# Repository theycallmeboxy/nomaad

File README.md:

# Nomaad
*A 11 column ortho/alpha gaming keyboard for gamers*

**[KLE](https://www.keyboard-layout-editor.com/##@_name=Nomaad%20Vial&author=theycallmeboxy%3B&@_x:0.5%3B&=0,1&=0,2&=0,3&=0,4&=0,5%3B&@=1,0&=1,1&=1,2&=1,3&=1,4&=1,5&=1,6&=1,7&=1,8&=1,9&=1,10%3B&@=2,0&=2,1&=2,2&=2,3&=2,4&=2,5&=2,6&=2,7&=2,8&=2,9&=2,10%3B&@_c=%2300c5ff%3B&=3,0%0A%0A%0A0,0&=3,1%0A%0A%0A0,0&=3,2%0A%0A%0A0,0&=3,3%0A%0A%0A0,0&=3,4%0A%0A%0A0,0&=3,5%0A%0A%0A0,0&=3,6%0A%0A%0A0,0&=3,7%0A%0A%0A0,0&=3,8%0A%0A%0A0,0&=3,9%0A%0A%0A0,0&=3,10%0A%0A%0A0,0%3B&@_c=%23cccccc%3B&=4,0&_x:1&c=%23ffb80c%3B&=4,1%0A%0A%0A1,0&_w:3%3B&=4,3%0A%0A%0A1,0&_w:2%3B&=4,6%0A%0A%0A1,0&=4,7%0A%0A%0A1,0&_x:1&c=%23cccccc%3B&=4,10%3B&@_y:0.5&c=%2300c5ff&w:1.5%3B&=3,0%0A%0A%0A0,1&=3,1%0A%0A%0A0,1&=3,2%0A%0A%0A0,1&=3,3%0A%0A%0A0,1&=3,4%0A%0A%0A0,1&=3,5%0A%0A%0A0,1&=3,6%0A%0A%0A0,1&=3,7%0A%0A%0A0,1&=3,8%0A%0A%0A0,1&_w:1.5%3B&=3,10%0A%0A%0A0,1%3B&@_y:0.25&x:2&c=%23ffb80c&w:7%3B&=4,3%0A%0A%0A1,1)**

## Production Files:

*(Click a link then click download icon in the top right to save a given file to your computer.)*

> [!CAUTION]
> I will assume no responsibility for any cost, damage, or sads resulting from trying to make one of my dumb projects. This project has no implicit support, neither moral nor technical.
> 
> **I'm not a doctor. This is not medical advice. I'm also only a network engineer. You assume all liability in using or reproducing these files.**

Case:
- [Case .stl file](https://github.com/theycallmeboxy/nomaad/blob/main/models/case/nomaad-case.stl)
- [Case .step file](https://github.com/theycallmeboxy/nomaad/blob/main/models/case/nomaad-case.step)

Plate:
- [Ortho stagger plate .dxf file](https://github.com/theycallmeboxy/nomaad/blob/main/models/plate/nomaad-plate_ortho.dxf)
- [Alpha stagger plate .dxf file](https://github.com/theycallmeboxy/nomaad/blob/main/models/plate/nomaad-plate_alpha.dxf)

PCB:
> [!NOTE]
> Version 1 was produced (as prototype 1) without any identified issues.  The gerbers were regenerated to indicate version 1 on the silk and the bom and positions files should be fixed to order as-is.  I have not produced these files yet, but they should be good to go.

- [PCB gerbers .zip file](https://github.com/theycallmeboxy/nomaad/blob/main/pcb/nomaad%20v1/production/nomaad.zip)
- [BOM .csv file](https://github.com/theycallmeboxy/nomaad/blob/main/pcb/nomaad%20v1/production/bom.csv)
- [Positions .csv file](https://github.com/theycallmeboxy/nomaad/blob/main/pcb/nomaad%20v1/production/positions.csv)

Firmware:
- [VIAL Firmware .bin file](https://github.com/theycallmeboxy/nomaad/blob/main/firmware/vial/binary/boxy_nomaad_vial.bin)
  
## Build Notes:

I have made with FDM and CNC aluminum to good effect.  Another 40s member had a resin version manufactured successfully.

**Additional materials:**
 
  - About 18" of .139" (3.53mm) cross section o-ring cord [like this 50A cord](https://www.theoringstore.com/store/index.php?main_page=product_info&cPath=117_527&products_id=18618) or [this 70A cord](https://www.theoringstore.com/store/index.php?main_page=product_info&cPath=117_119&products_id=5058); if you don't want to buy bulk cord, you can cut up an o-ring of like 6" or bigger diameter.
  - 4 SKUF feet like these  [like these](https://keeb.io/products/skuf-silicone-rubber-keyboard-feet).

**Build instructions:**

1. Apply feet to the cutouts.
2. Install stabs if you're into that. 
3. Install switches into the plate and PCB.
4. Solder it up.
5. Friction fit the o-ring cord between the plate and PCB in the positions highlighted in red:

6. Insert the assembled PCB number keys first into the case at an angle while aligning the USB port with the cutout.
7. Press the top of the PCB in place, then press in the bottom side (if your cord isn't fully seated, sticks out on the corners, or otherwise catches going in, grab some tweezers and help it stay in between the plate and PCB). 
8. If you need to remove the PCB, pull a few caps off and use a switch puller on the soldered switches.

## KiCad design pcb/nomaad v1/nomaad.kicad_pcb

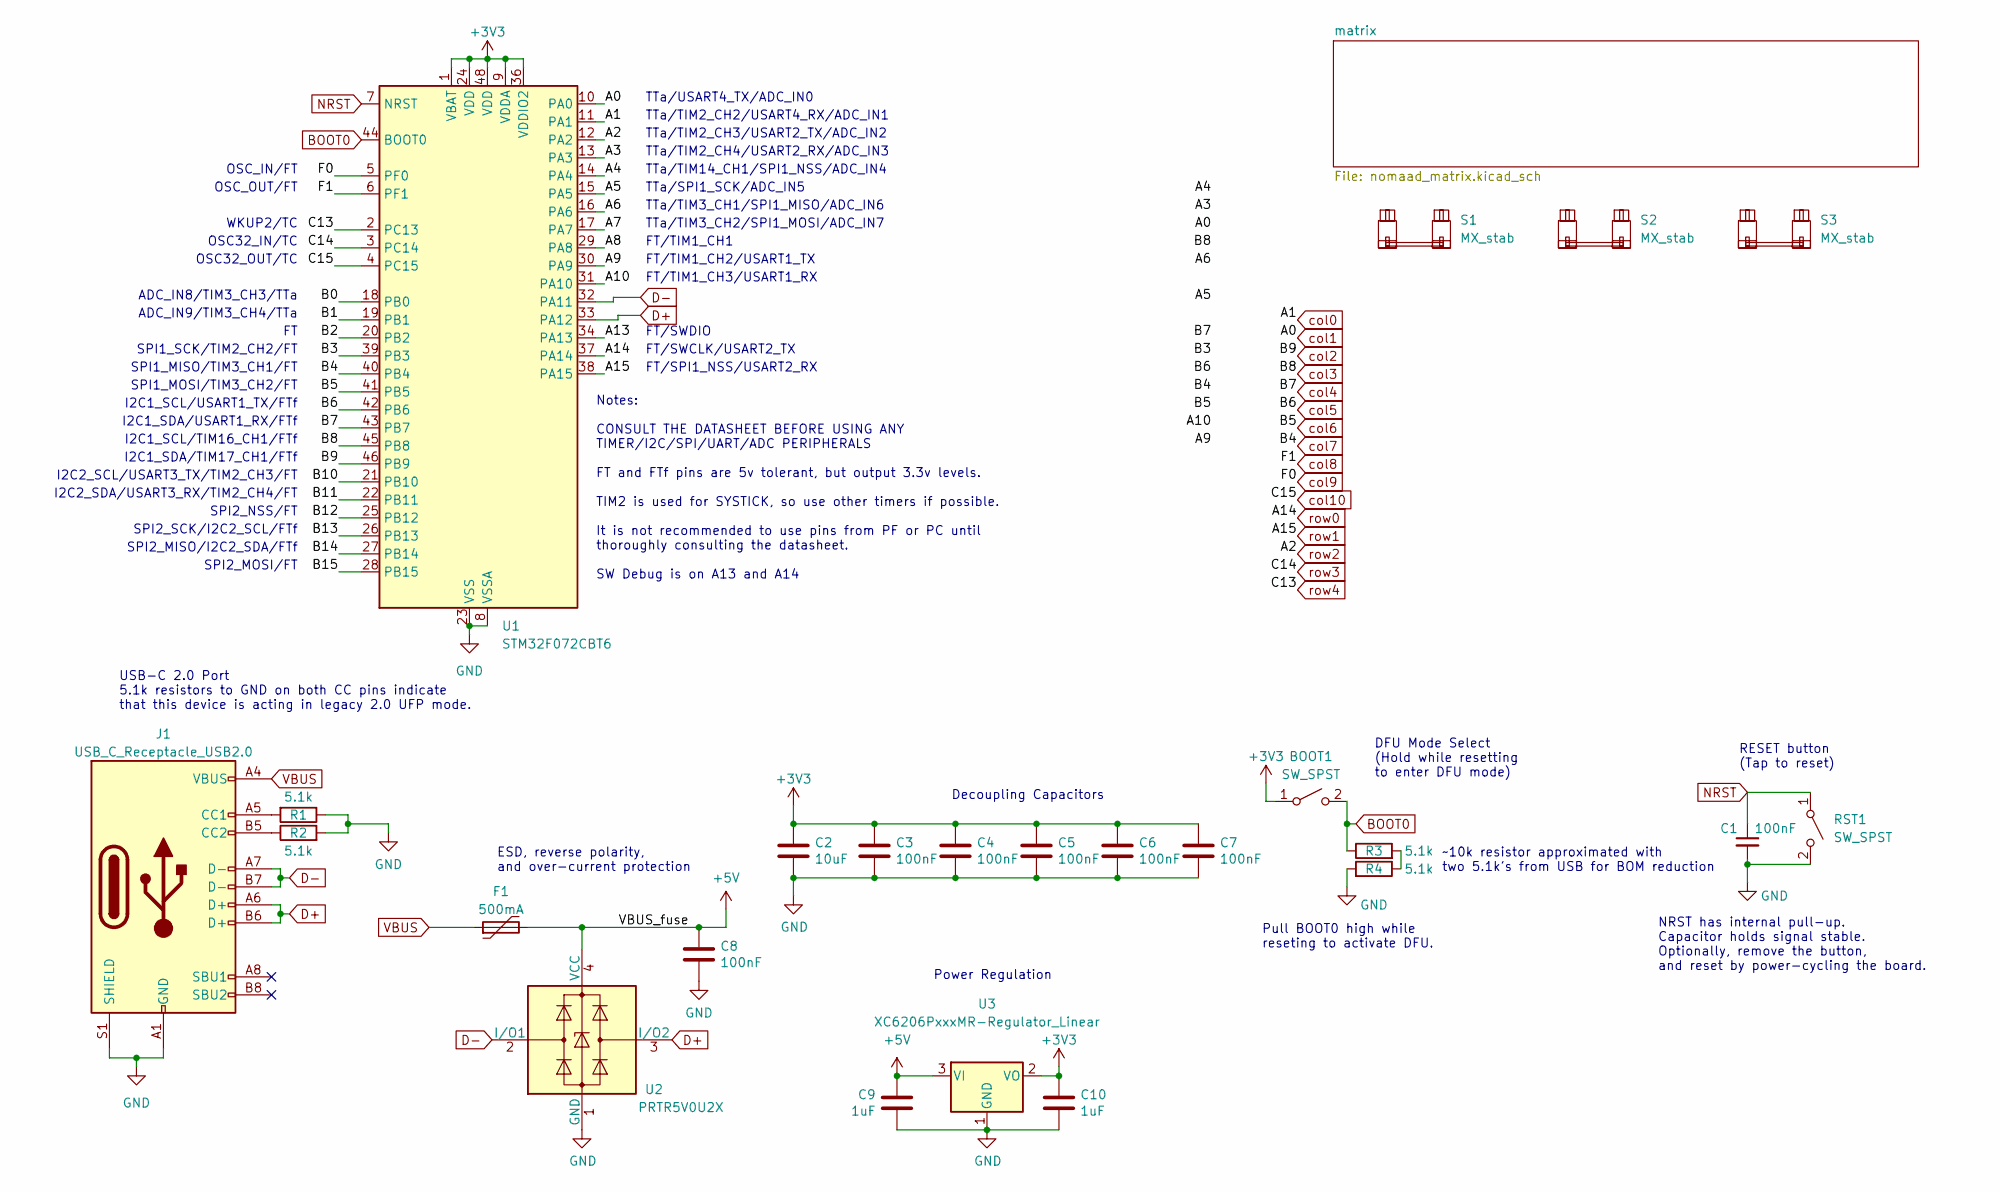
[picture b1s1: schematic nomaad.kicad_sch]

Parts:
BOOT1: SW_SPST; SW_SPST_TL3342
C1, C3, C4, C5, C6, C7, C8: 100nF; C_0402_1005Metric; LCSC C307331
C2: 10uF; C_0603_1608Metric; LCSC C307331
C9, C10: 1uF; C_0402_1005Metric; LCSC C307331
F1: 500mA; Fuse_1206_3216Metric; LCSC C135341
J1: USB_C_Receptacle_USB2.0; USB_C_Receptacle_HRO_TYPE-C-31-M-12; JlcRotOffset 180
R1, R2, R3, R4: 5.1k; R_0402_1005Metric
RST1: SW_SPST; SW_SPST_TL3342
S1: MX_stab; STAB_MX_7u
S2: MX_stab; STAB_MX_2u
S3: MX_stab; STAB_MX_3u
U1: STM32F072CBT6; LQFP-48_7x7mm_P0.5mm; JlcRotOffset 90
U2: PRTR5V0U2X; SOT-143; LCSC C2827688
U3: XC6206PxxxMR-Regulator_Linear; SOT-23; LCSC C5446

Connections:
+3V3: BOOT1.1 (A), C2.1, C3.1, C4.1, C5.1, C6.1, C7.1, C10.1, U1.1 (VBAT), U1.9 (VDDA), U1.24 (VDD), U1.36 (VDDIO2), U1.48 (VDD), U3.2 (VO)
+5V: C8.1, C9.1, F1.2, U2.4 (VCC), U3.3 (VI)
/A3: U1.13 (PA3)
/A4: U1.14 (PA4)
/A5: U1.15 (PA5)
/A6: U1.16 (PA6)
/A7: U1.17 (PA7)
/A8: U1.29 (PA8)
/A9: U1.30 (PA9)
/A10: U1.31 (PA10)
/A13: U1.34 (PA13)
/B0: U1.18 (PB0)
/B1: U1.19 (PB1)
/B2: U1.20 (PB2)
/B3: U1.39 (PB3)
/B10: U1.21 (PB10)
/B11: U1.22 (PB11)
/B12: U1.25 (PB12)
/B13: U1.26 (PB13)
/B14: U1.27 (PB14)
/B15: U1.28 (PB15)
BOOT0: BOOT1.2 (B), R3.1, U1.44 (BOOT0)
D+: J1.A6 (D+), J1.B6 (D+), U1.33 (PA12), U2.3 (I/O2)
D-: J1.A7 (D-), J1.B7 (D-), U1.32 (PA11), U2.2 (I/O1)
GND: C1.2, C2.2, C3.2, C4.2, C5.2, C6.2, C7.2, C8.2, C9.2, C10.2, J1.A1 (GND), J1.A12 (GND), J1.B1 (GND), J1.B12 (GND), J1.S1 (SHIELD), R1.1, R2.2, R4.2, RST1.2 (B), U1.8 (VSSA), U1.23 (VSS), U1.35 (VSS), U1.47 (VSS), U2.1 (GND), U3.1 (GND)
NRST: C1.1, RST1.1 (A), U1.7 (NRST)
unnamed: J1.A5 (CC1), R1.2
unnamed: J1.B5 (CC2), R2.1
unnamed: R3.2, R4.1
VBUS: F1.1, J1.A4 (VBUS), J1.A9 (VBUS), J1.B4 (VBUS), J1.B9 (VBUS)
col0: U1.11 (PA1); also elsewhere on the board
col1: U1.10 (PA0); also elsewhere on the board
col2: U1.46 (PB9); also elsewhere on the board
col3: U1.45 (PB8); also elsewhere on the board
col4: U1.43 (PB7); also elsewhere on the board
col5: U1.42 (PB6); also elsewhere on the board
col6: U1.41 (PB5); also elsewhere on the board
col7: U1.40 (PB4); also elsewhere on the board
col8: U1.6 (PF1); also elsewhere on the board
col9: U1.5 (PF0); also elsewhere on the board
col10: U1.4 (PC15); also elsewhere on the board
row0: U1.37 (PA14); also elsewhere on the board
row1: U1.38 (PA15); also elsewhere on the board
row2: U1.12 (PA2); also elsewhere on the board
row3: U1.3 (PC14); also elsewhere on the board
row4: U1.2 (PC13); also elsewhere on the board

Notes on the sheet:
I2C2_SCL/USART3_TX/TIM2_CH3/FT
TTa/TIM2_CH2/USART4_RX/ADC_IN1
OSC_IN/FT
Decoupling Capacitors
DFU Mode Select (Hold while resetting to enter DFU mode)
OSC32_IN/TC
SPI2_MISO/I2C2_SDA/FTf
SPI2_MOSI/FT
SPI1_SCK/TIM2_CH2/FT
I2C2_SDA/USART3_RX/TIM2_CH4/FT
OSC_OUT/FT
Power Regulation
TTa/TIM14_CH1/SPI1_NSS/ADC_IN4
Pull BOOT0 high while reseting to activate DFU.
FT/TIM1_CH2/USART1_TX
SPI2_SCK/I2C2_SCL/FTf
ADC_IN8/TIM3_CH3/TTa
TTa/SPI1_SCK/ADC_IN5
I2C1_SDA/TIM17_CH1/FTf
I2C1_SCL/USART1_TX/FTf
WKUP2/TC
FT/TIM1_CH1
TTa/USART4_TX/ADC_IN0
USB-C 2.0 Port 5.1k resistors to GND on both CC pins indicate that this device is acting in legacy 2.0 UFP mode.
ESD, reverse polarity, and over-current protection
NRST has internal pull-up. Capacitor holds signal stable. Optionally, remove the button, and reset by power-cycling the board.
OSC32_OUT/TC
~10k resistor approximated with two 5.1k's from USB for BOM reduction
I2C1_SDA/USART1_RX/FTf
TTa/TIM3_CH2/SPI1_MOSI/ADC_IN7
TTa/TIM2_CH4/USART2_RX/ADC_IN3
ADC_IN9/TIM3_CH4/TTa
SPI1_MOSI/TIM3_CH2/FT
FT/SPI1_NSS/USART2_RX
FT/SWCLK/USART2_TX
SPI2_NSS/FT
FT/SWDIO
I2C1_SCL/TIM16_CH1/FTf
FT/TIM1_CH3/USART1_RX
TTa/TIM3_CH1/SPI1_MISO/ADC_IN6

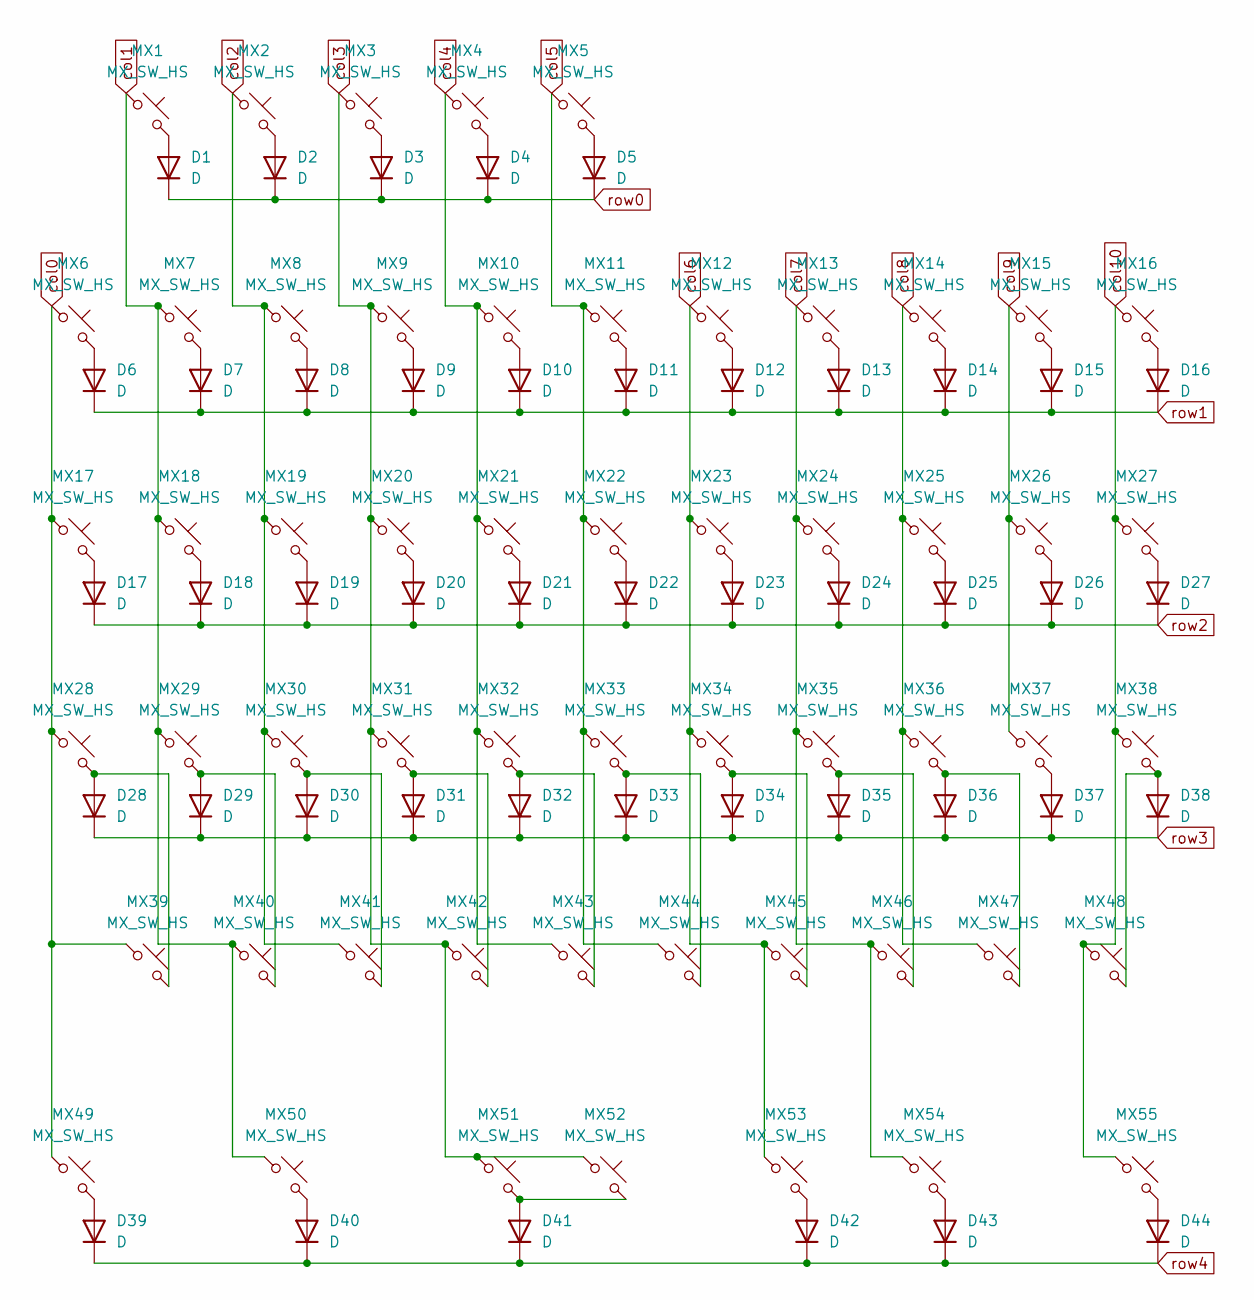
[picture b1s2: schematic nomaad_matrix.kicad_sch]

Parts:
D1, D2, D3, D4, D5, D6, D7, D8, D9, D10, D11, D12, D13, D14, D15, D16, D17, D18, D19, D20, D21, D22, D23, D24, D25, D26, D27, D28, D29, D30, D31, D32, D33, D34, D35, D36, D37, D38, D39, D40, D41, D42, D43, D44: D; D_SOD-123
MX1, MX2, MX3, MX4, MX5, MX6, MX7, MX8, MX9, MX10, MX11, MX12, MX13, MX14, MX15, MX16, MX17, MX18, MX19, MX20, MX21, MX22, MX23, MX24, MX25, MX26, MX27, MX28, MX29, MX30, MX31, MX32, MX33, MX34, MX35, MX36, MX37, MX38, MX39, MX40, MX41, MX42, MX43, MX44, MX45, MX46, MX47, MX48, MX49, MX50, MX51, MX52, MX53, MX54, MX55: MX_SW_HS; SW_MX_1u

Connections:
unnamed: D1.2 (A), MX1.2
unnamed: D2.2 (A), MX2.2
unnamed: D3.2 (A), MX3.2
unnamed: D4.2 (A), MX4.2
unnamed: D5.2 (A), MX5.2
unnamed: D6.2 (A), MX6.2
unnamed: D7.2 (A), MX7.2
unnamed: D8.2 (A), MX8.2
unnamed: D9.2 (A), MX9.2
unnamed: D10.2 (A), MX10.2
unnamed: D11.2 (A), MX11.2
unnamed: D12.2 (A), MX12.2
unnamed: D13.2 (A), MX13.2
unnamed: D14.2 (A), MX14.2
unnamed: D15.2 (A), MX15.2
unnamed: D16.2 (A), MX16.2
unnamed: D17.2 (A), MX17.2
unnamed: D18.2 (A), MX18.2
unnamed: D19.2 (A), MX19.2
unnamed: D20.2 (A), MX20.2
unnamed: D21.2 (A), MX21.2
unnamed: D22.2 (A), MX22.2
unnamed: D23.2 (A), MX23.2
unnamed: D24.2 (A), MX24.2
unnamed: D25.2 (A), MX25.2
unnamed: D26.2 (A), MX26.2
unnamed: D27.2 (A), MX27.2
unnamed: D28.2 (A), MX28.2, MX39.2
unnamed: D29.2 (A), MX29.2, MX40.2
unnamed: D30.2 (A), MX30.2, MX41.2
unnamed: D31.2 (A), MX31.2, MX42.2
unnamed: D32.2 (A), MX32.2, MX43.2
unnamed: D33.2 (A), MX33.2, MX44.2
unnamed: D34.2 (A), MX34.2, MX45.2
unnamed: D35.2 (A), MX35.2, MX46.2
unnamed: D36.2 (A), MX36.2, MX47.2
unnamed: D37.2 (A), MX37.2
unnamed: D38.2 (A), MX38.2, MX48.2
unnamed: D39.2 (A), MX49.2
unnamed: D40.2 (A), MX50.2
unnamed: D41.2 (A), MX51.2, MX52.2
unnamed: D42.2 (A), MX53.2
unnamed: D43.2 (A), MX54.2
unnamed: D44.2 (A), MX55.2
col0: MX6.1, MX17.1, MX28.1, MX39.1, MX49.1; also elsewhere on the board
col1: MX1.1, MX7.1, MX18.1, MX29.1, MX40.1, MX50.1; also elsewhere on the board
col2: MX2.1, MX8.1, MX19.1, MX30.1, MX41.1; also elsewhere on the board
col3: MX3.1, MX9.1, MX20.1, MX31.1, MX42.1, MX51.1, MX52.1; also elsewhere on the board
col4: MX4.1, MX10.1, MX21.1, MX32.1, MX43.1; also elsewhere on the board
col5: MX5.1, MX11.1, MX22.1, MX33.1, MX44.1; also elsewhere on the board
col6: MX12.1, MX23.1, MX34.1, MX45.1, MX53.1; also elsewhere on the board
col7: MX13.1, MX24.1, MX35.1, MX46.1, MX54.1; also elsewhere on the board
col8: MX14.1, MX25.1, MX36.1, MX47.1; also elsewhere on the board
col9: MX15.1, MX26.1, MX37.1; also elsewhere on the board
col10: MX16.1, MX27.1, MX38.1, MX48.1, MX55.1; also elsewhere on the board
row0: D1.1 (K), D2.1 (K), D3.1 (K), D4.1 (K), D5.1 (K); also elsewhere on the board
row1: D6.1 (K), D7.1 (K), D8.1 (K), D9.1 (K), D10.1 (K), D11.1 (K), D12.1 (K), D13.1 (K), D14.1 (K), D15.1 (K), D16.1 (K); also elsewhere on the board
row2: D17.1 (K), D18.1 (K), D19.1 (K), D20.1 (K), D21.1 (K), D22.1 (K), D23.1 (K), D24.1 (K), D25.1 (K), D26.1 (K), D27.1 (K); also elsewhere on the board
row3: D28.1 (K), D29.1 (K), D30.1 (K), D31.1 (K), D32.1 (K), D33.1 (K), D34.1 (K), D35.1 (K), D36.1 (K), D37.1 (K), D38.1 (K); also elsewhere on the board
row4: D39.1 (K), D40.1 (K), D41.1 (K), D42.1 (K), D43.1 (K), D44.1 (K); also elsewhere on the board

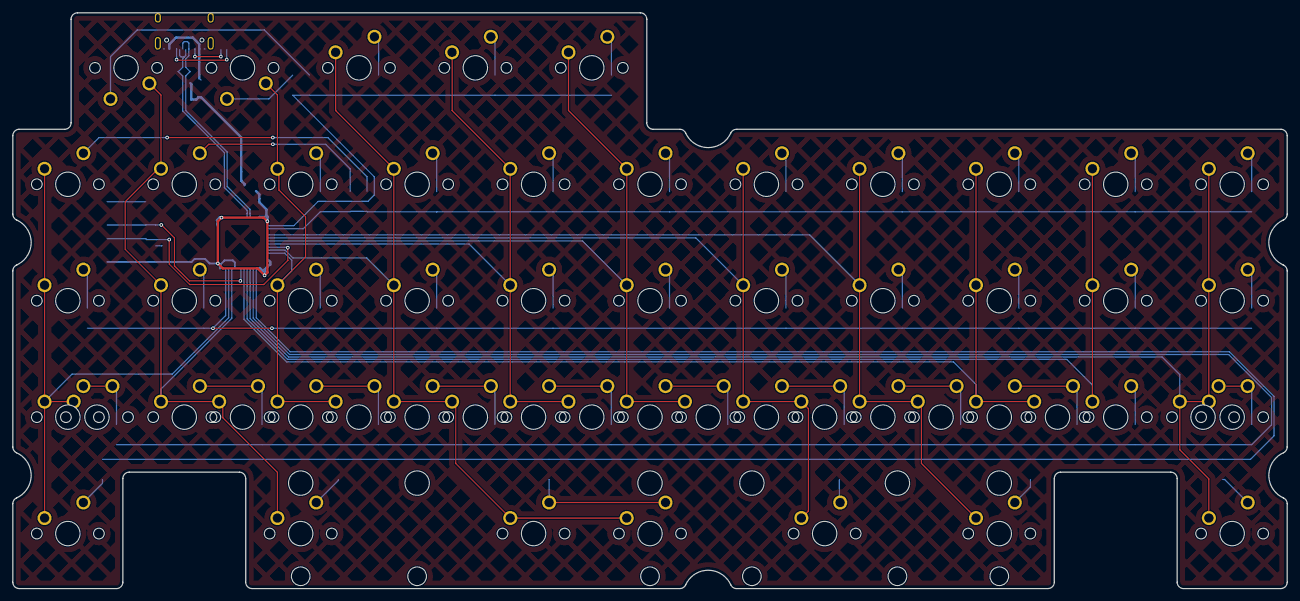
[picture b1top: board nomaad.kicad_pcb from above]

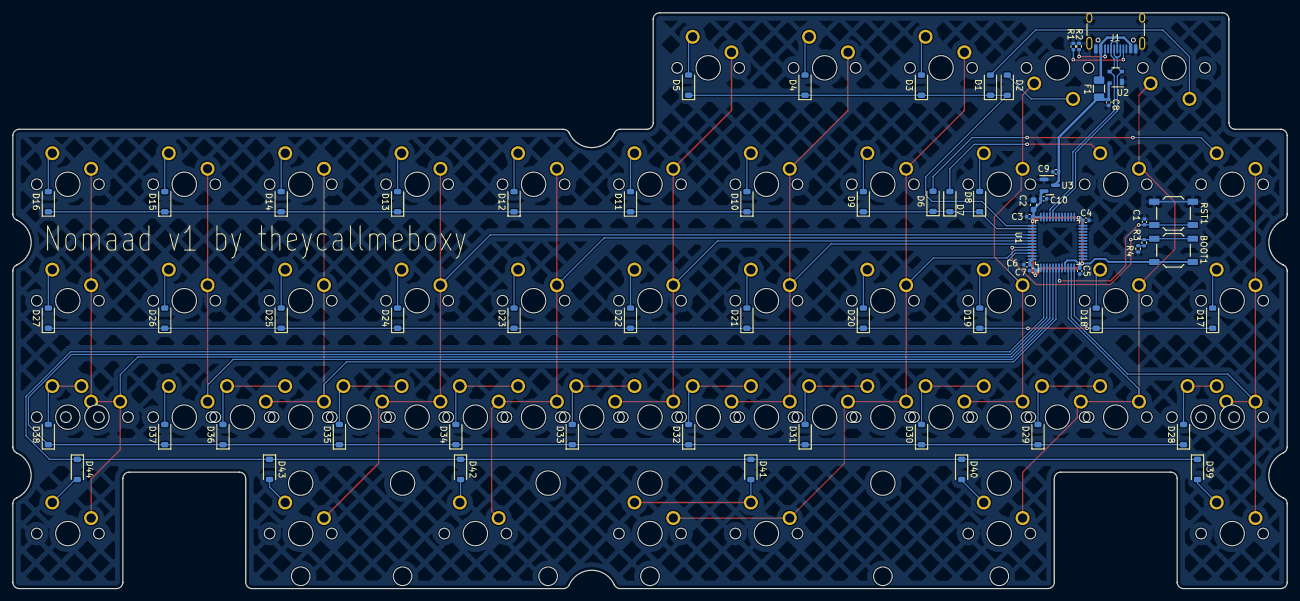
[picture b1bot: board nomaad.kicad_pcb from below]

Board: 2 copper layers, 208.5 x 94.2 mm, 123 parts (65 on the bottom side), 71 nets.

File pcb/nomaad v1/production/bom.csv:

Designator,Footprint,Quantity,Value,LCSC Part #
"BOOT1, RST1",SW_SPST_TL3342,2,SW_SPST,C318884
"C1, C3, C4, C5, C6, C7, C8",0402,7,100nF,C1525
"C10, C9",0402,2,1uF,C52923
C2,0603,1,10uF,C19702
"D1, D10, D11, D12, D13, D14, D15, D16, D17, D18, D19, D2, D20, D21, D22, D23, D24, D25, D26, D27, D28, D29, D3, D30, D31, D32, D33, D34, D35, D36, D37, D38, D39, D4, D40, D41, D42, D43, D44, D5, D6, D7, D8, D9",D_SOD-123,44,D,C81598
F1,1206,1,500mA,C369160
J1,USB_C_Receptacle_HRO_TYPE-C-31-M-12,1,USB_C_Receptacle_USB2.0,C165948
"R1, R2, R3, R4",0402,4,5.1k,C25905
U1,LQFP-48_7x7mm_P0.5mm,1,STM32F072CBT6,C81720
U2,SOT-143,1,PRTR5V0U2X,C2827688
U3,SOT-23,1,XC6206PxxxMR-Regulator_Linear,C5446

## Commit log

2024-10-03 here comes the sun
